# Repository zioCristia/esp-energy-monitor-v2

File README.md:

# Esp energy monitor - Version 2
Esp32 based module, 220V ac powered, energy monitor with three ct sensors (for solar power, home power and air conditioning power), and an LCD I2C display for visualization. Integrated with ESPhome in my IoT house based in Home Assistant.
Any possibility of improvement is accepted.

The board's design allows it to be inserted into the rail of the home's breaker box by printing a 3D component.

### Added features
This is an update of the previous [version](https://github.com/zioCristia/esp-energy-monitor-v1) where I added a third sensor for reading the consumption of air conditioners and the possibility of adding additional boards for future ideas.
[Here](https://github.com/zioCristia/smart-irrigation-control-unit) you can find a compatible board to add smart garden irrigation functionality to the board.

The board's design also allows it to be inserted into the rail of the home's breaker box by printing a 3D component.

## Table of contents
* [General info](#general-info)
* [Hardware](#hardware)
* [Software](#software)
* [Pcb](#pcb)
* [Compatible shields](#compatible-shields)
* [Contribution](#contribution)

# General info
This is the second version of a simple energy monitor I built for my home. It has three ct sensors that control the current of the solar panels production, the house consumption and the air conditioning. These sensors are controlled by an esp32 board for connection via wi-fi to the home assistant thanks to the Esphome software. 

The board could be powered with a 220V ac, so no external transformer is needed, but for extensive use, especially when connected to some board extensions, it is recommended to use an external one and plug it directly into the 5V holes.

I have also added a 16x2 lcd so that I can have an immediate output in my electrical service panel.

The total cost for a board with three CT sensors (included) is around 25/30€.

# Hardware
The module is composed of:

* esp32
* sct 013 030 30A/1V as ct sensor, x3
* 16x2 lcd display with i2c interface
* 3.5mm jack connector with 5 pin, x3
* 10k ohm resistor, x6
* 10uF capacitor, x4
* 75ohm resistor, x3 (not mandatory, depending on the CT sensor)

A list with the main components and links could be found [here](https://docs.google.com/spreadsheets/d/1uGH7hN6ZSQ5MoKFjuWFCn1lEjyLJ1oxg2DWpdToigKc/edit#gid=1313427219).
The burden resistor (75ohm) should be added depending on the CT sensor. In that case, to have the best readings, it should be changed based on the max current you are going to measure with the ct sensors, according to the following formula present in [openenergymonitor](https://docs.openenergymonitor.org/electricity-monitoring/ct-sensors/interface-with-arduino.html) page:

```
Burden Resistor (ohms) = (AREF * CT TURNS) / (2√2 * max primary current)
```

# Software
The software I have used is EspHome in order to integrate the sensor with my HomeAssistant server but you may as well use another software to your liking.
You can see [here](https://github.com/zioCristia/esp-energy-monitor-v2/blob/main/energy_monitor.yaml.exemple) an example of the software uploaded on the board.

The filter section is used to obtain the right value of current from the sensor. I've done it confronting the values read with a well know source (like a phone or an electric heater).
Moreover I've added a part to read zero values when we are near zero due to some interference that never allows to have values equal to zero.
```
filters:
      - calibrate_linear:
          # Measured value of 0.0065 maps to 0A
          - 0.0065 -> 0
          # Known load: 13.783A
          # Value shown in logs: 0.2348A
          - 0.2348 -> 13.783
      - lambda: |-
          if (x > 0.2) return x;
          else return 0;
```

I've added a software sensor which gives me the difference between the in power and the out power with which I do some automation in home assistant and allows me to maximize the usage of current produced by the solar panels.

The toGridEnergy and the toGridPower is used to interface with the new energy management feature in home assistant.

The lcd prints the solar power as IN, home power as OUT, the hour in the top right and below the difference between IN-OUT, so the differencePower.

# Pcb
The pcb layout is extremely simple with enough space for all the parts. The components are all through hole and the female jack connector is with 5 pins. Anyone can make this pcb at home with just a soldering iron.

You can find the whole eagle project in [this folder](https://github.com/zioCristia/esp-energy-monitor-v2/tree/main/esp-energy-monitor-v2).

The board's design allows it to be inserted into the rail of the home's breaker box by printing a 3D component.

# Compatible shields
* [Irrigation control unit](https://github.com/zioCristia/smart-irrigation-control-unit)
  
# Contribution
Feel free to report any bugs or feature requests.

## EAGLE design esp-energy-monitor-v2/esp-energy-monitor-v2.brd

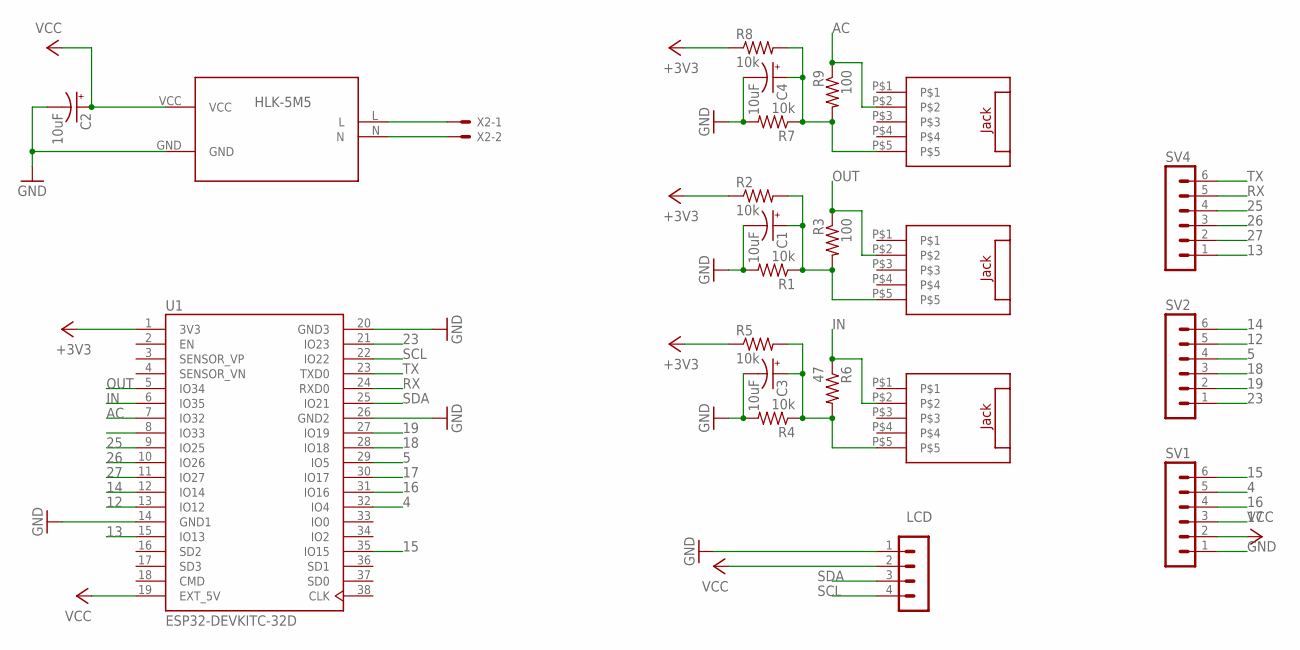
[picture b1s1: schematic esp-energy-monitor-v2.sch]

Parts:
ACJACK: JACK_5PINS
C1, C2, C3, C4: 10uF; B45181A
HLK-5M5: HLK-5M05; CONV_HLK-5M05
INJACK: JACK_5PINS
OUTJACK: JACK_5PINS
R1, R2, R4, R5, R7, R8: 10k; 0204/7
R3, R9: 100; 0204/7
R6: 47; 0204/7
SV1, SV2, SV4: MA06-1
SV3: MA04-1
U1: ESP32-DEVKITC-32D; MODULE_ESP32-DEVKITC-32D
X2: JST-XH-02-PIN-LONG-PAD; JST-XH-02-PACKAGE-LONG-PAD

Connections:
4: SV1.5, U1.32 (IO4)
5: SV2.4, U1.29 (IO5)
12: SV2.5, U1.13 (IO12)
13: SV4.1, U1.15 (IO13)
14: SV2.6, U1.12 (IO14)
15: SV1.6, U1.35 (IO15)
16: SV1.4, U1.31 (IO16)
17: SV1.3, U1.30 (IO17)
18: SV2.3, U1.28 (IO18)
19: SV2.2, U1.27 (IO19)
23: SV2.1, U1.21 (IO23)
25: SV4.4, U1.9 (IO25)
26: SV4.3, U1.10 (IO26)
27: SV4.2, U1.11 (IO27)
+3V3: R2.1, R5.1, R8.1, U1.1 (3V3)
AC: ACJACK.P$2, R9.1, U1.7 (IO32)
GND: C1.-, C2.-, C3.-, C4.-, HLK-5M5.GND, R1.2, R4.2, R7.2, SV1.1, SV3.1, U1.14 (GND1), U1.20 (GND3), U1.26 (GND2)
IN: INJACK.P$2, R6.1, U1.6 (IO35)
unnamed: HLK-5M5.N, X2.2
unnamed: HLK-5M5.L, X2.1
unnamed: C1.+, OUTJACK.P$5, R1.1, R2.2, R3.2
unnamed: ACJACK.P$5, C4.+, R7.1, R8.2, R9.2
unnamed: C3.+, INJACK.P$5, R4.1, R5.2, R6.2
OUT: OUTJACK.P$2, R3.1, U1.5 (IO34)
RX: SV4.5, U1.24 (RXD0)
SCL: SV3.4, U1.22 (IO22)
SDA: SV3.3, U1.25 (IO21)
TX: SV4.6, U1.23 (TXD0)
VCC: C2.+, HLK-5M5.VCC, SV1.2, SV3.2, U1.19 (EXT_5V)

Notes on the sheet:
HLK-5M5
LCD

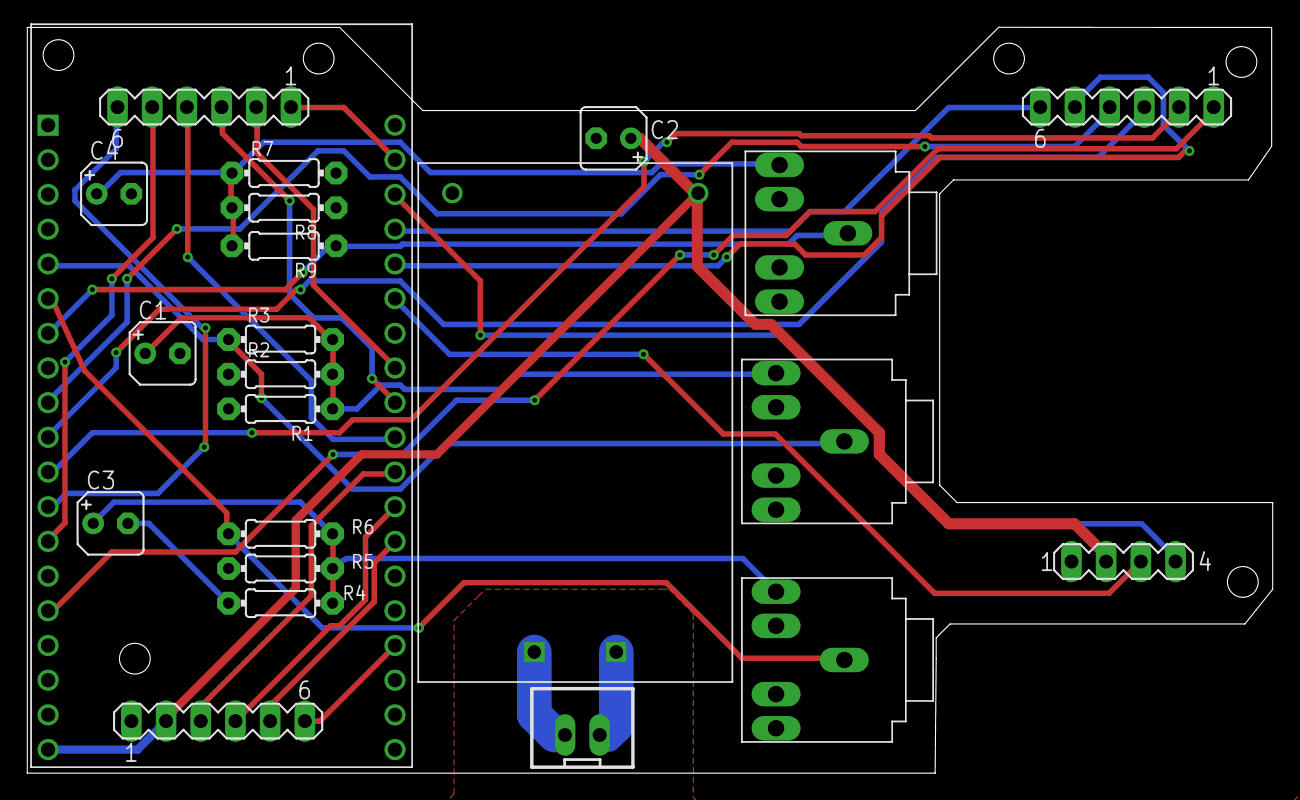
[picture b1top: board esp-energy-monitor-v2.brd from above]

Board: 2 copper layers, 91.2 x 54.6 mm, 23 parts (0 on the bottom side), 29 nets.

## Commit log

2025-05-25 Create LICENSE
